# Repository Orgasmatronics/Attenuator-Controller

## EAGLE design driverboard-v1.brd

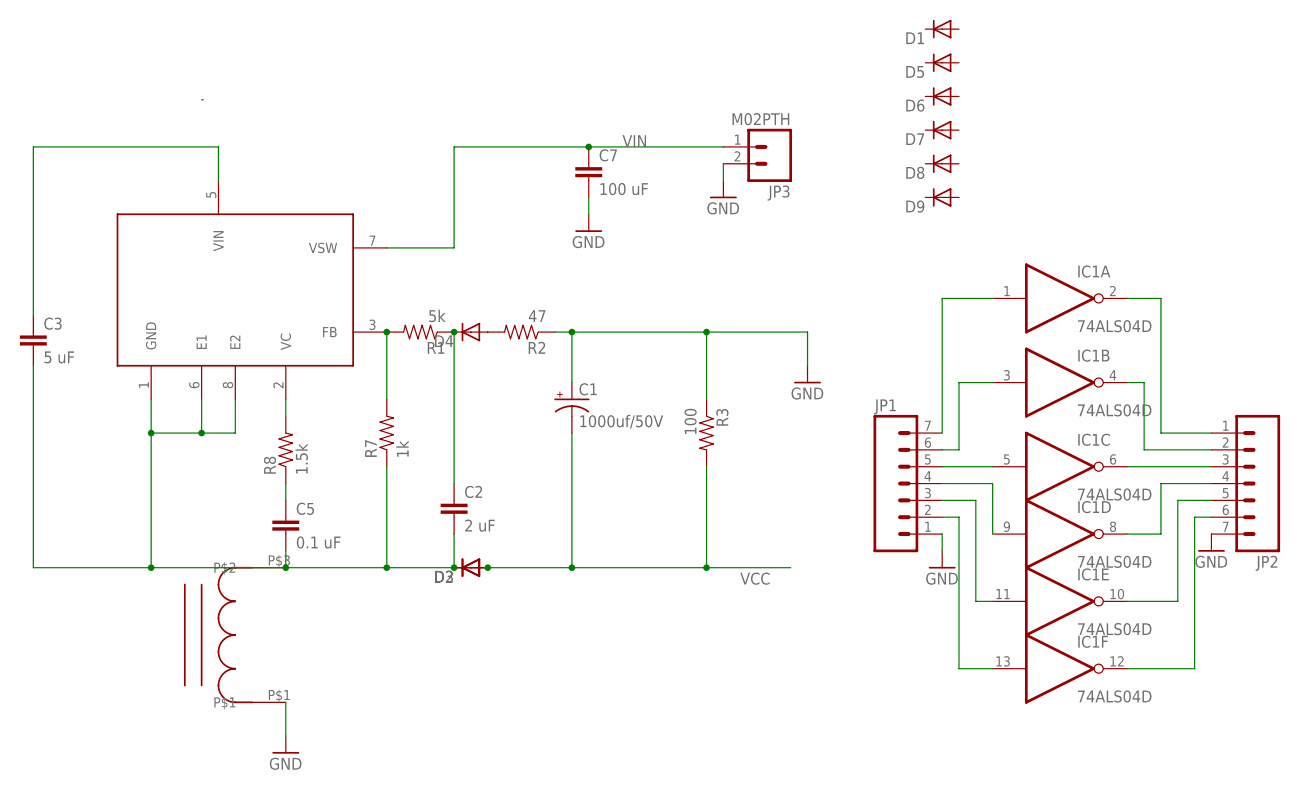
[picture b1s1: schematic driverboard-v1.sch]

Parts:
C1: 1000uf/50V; CPOL-RADIAL-1000UF-25V-KIT
C2: 2 uF; 0805
C3: 5 uF; 0805
C5: 0.1 uF; 0805
C7: 100 uF; 1206
D1, D2, D3, D4, D5, D6, D7, D8, D9: DIODE-DO-214AC; DO-214AC
IC1: 74ALS04D; SO14
JP1, JP2: M07; 1X07
JP3: M02PTH; 1X02
L2: 52626-L
R1: 5k; 0603-RES
R2: 47; 0603-RES
R3: 100; 0603-RES
R7: 1k; 0603-RES
R8: 1.5k; 0603-RES
U3: 1072-BOOST

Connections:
GND: C1.+, C7.2, IC1.7 (GND), JP1.1, JP2.7, JP3.2, L2.P$1, R2.1, R3.1
unnamed: IC1.1 (I), JP1.7
unnamed: R1.2, R7.2, U3.3 (FB)
unnamed: C2.1, D4.C, R1.1
unnamed: C3.1, U3.5 (VIN)
unnamed: C5.1, R8.1
unnamed: D4.A, R2.2
unnamed: C2.2, C3.2, C5.2, D2.C, D3.C, L2.P$3, R7.1, U3.1 (GND), U3.6 (E1), U3.8 (E2)
unnamed: IC1.3 (I), JP1.6
unnamed: IC1.5 (I), JP1.5
unnamed: IC1.9 (I), JP1.4
unnamed: IC1.11 (I), JP1.3
unnamed: IC1.13 (I), JP1.2
unnamed: IC1.12 (O), JP2.6
unnamed: IC1.10 (O), JP2.5
unnamed: IC1.8 (O), JP2.4
unnamed: IC1.6 (O), JP2.3
unnamed: IC1.4 (O), JP2.2
unnamed: IC1.2 (O), JP2.1
unnamed: R8.2, U3.2 (VC)
VCC: C1.-, D2.A, D3.A, IC1.14 (VCC), R3.2
VIN: C7.1, JP3.1, U3.7 (VSW)

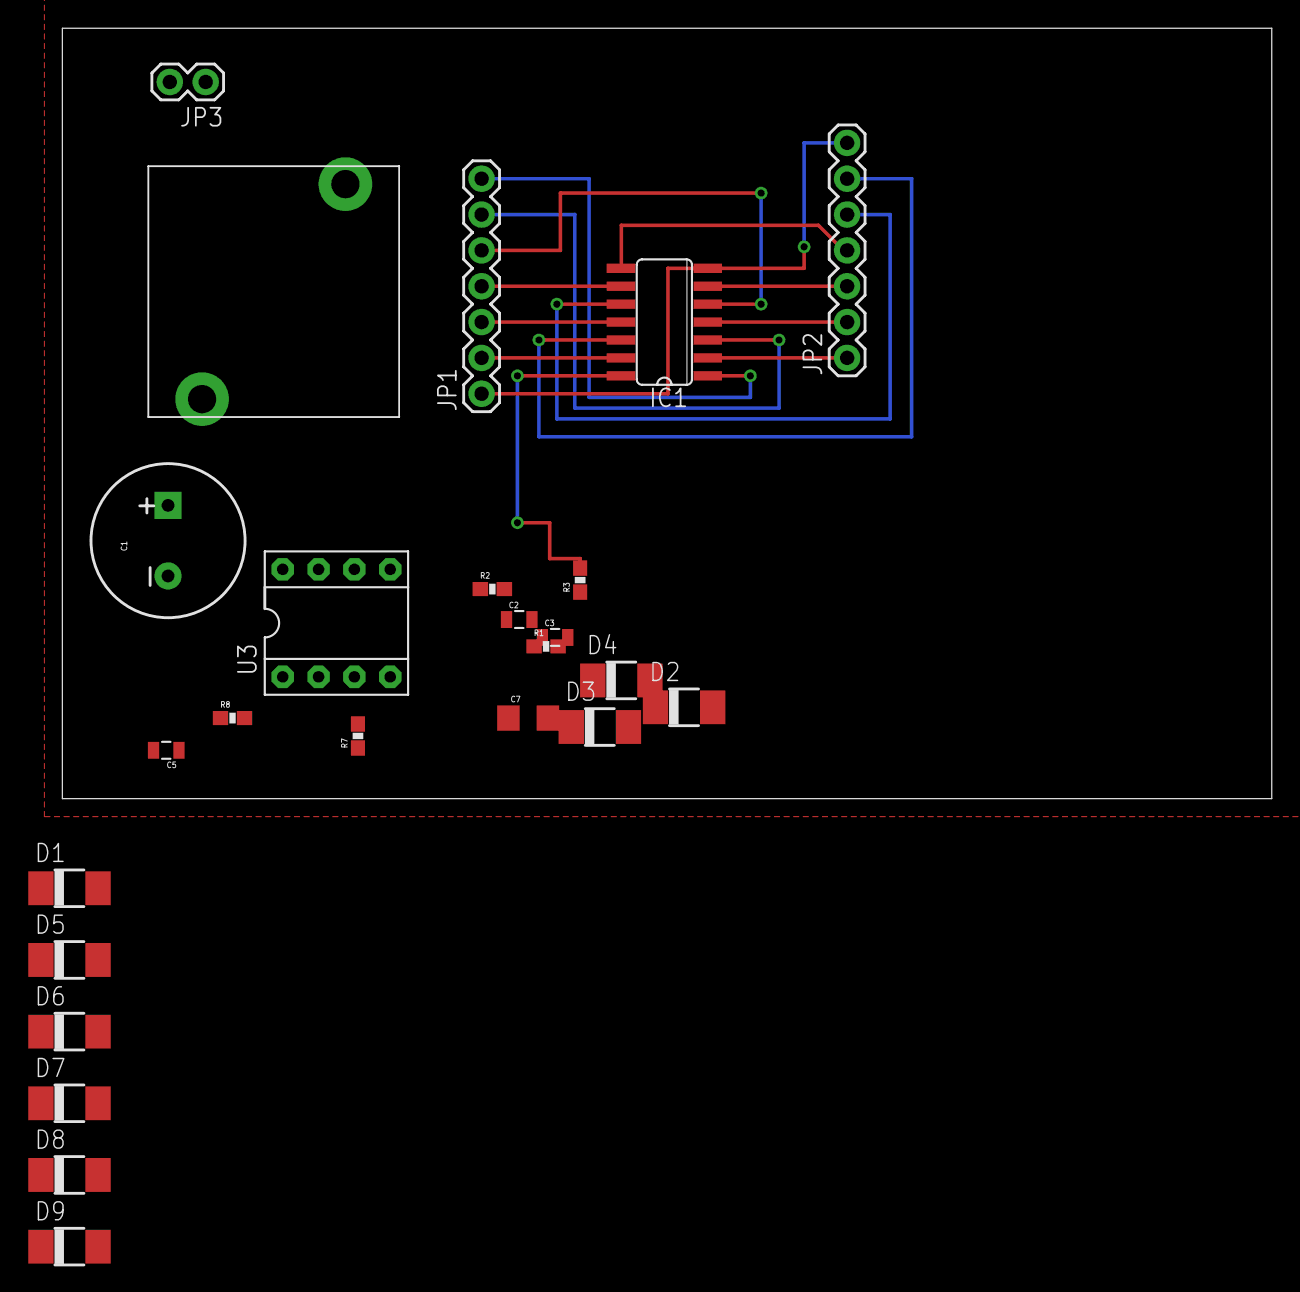
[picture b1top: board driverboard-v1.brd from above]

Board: 2 copper layers, 85.7 x 54.6 mm, 25 parts (0 on the bottom side), 22 nets.

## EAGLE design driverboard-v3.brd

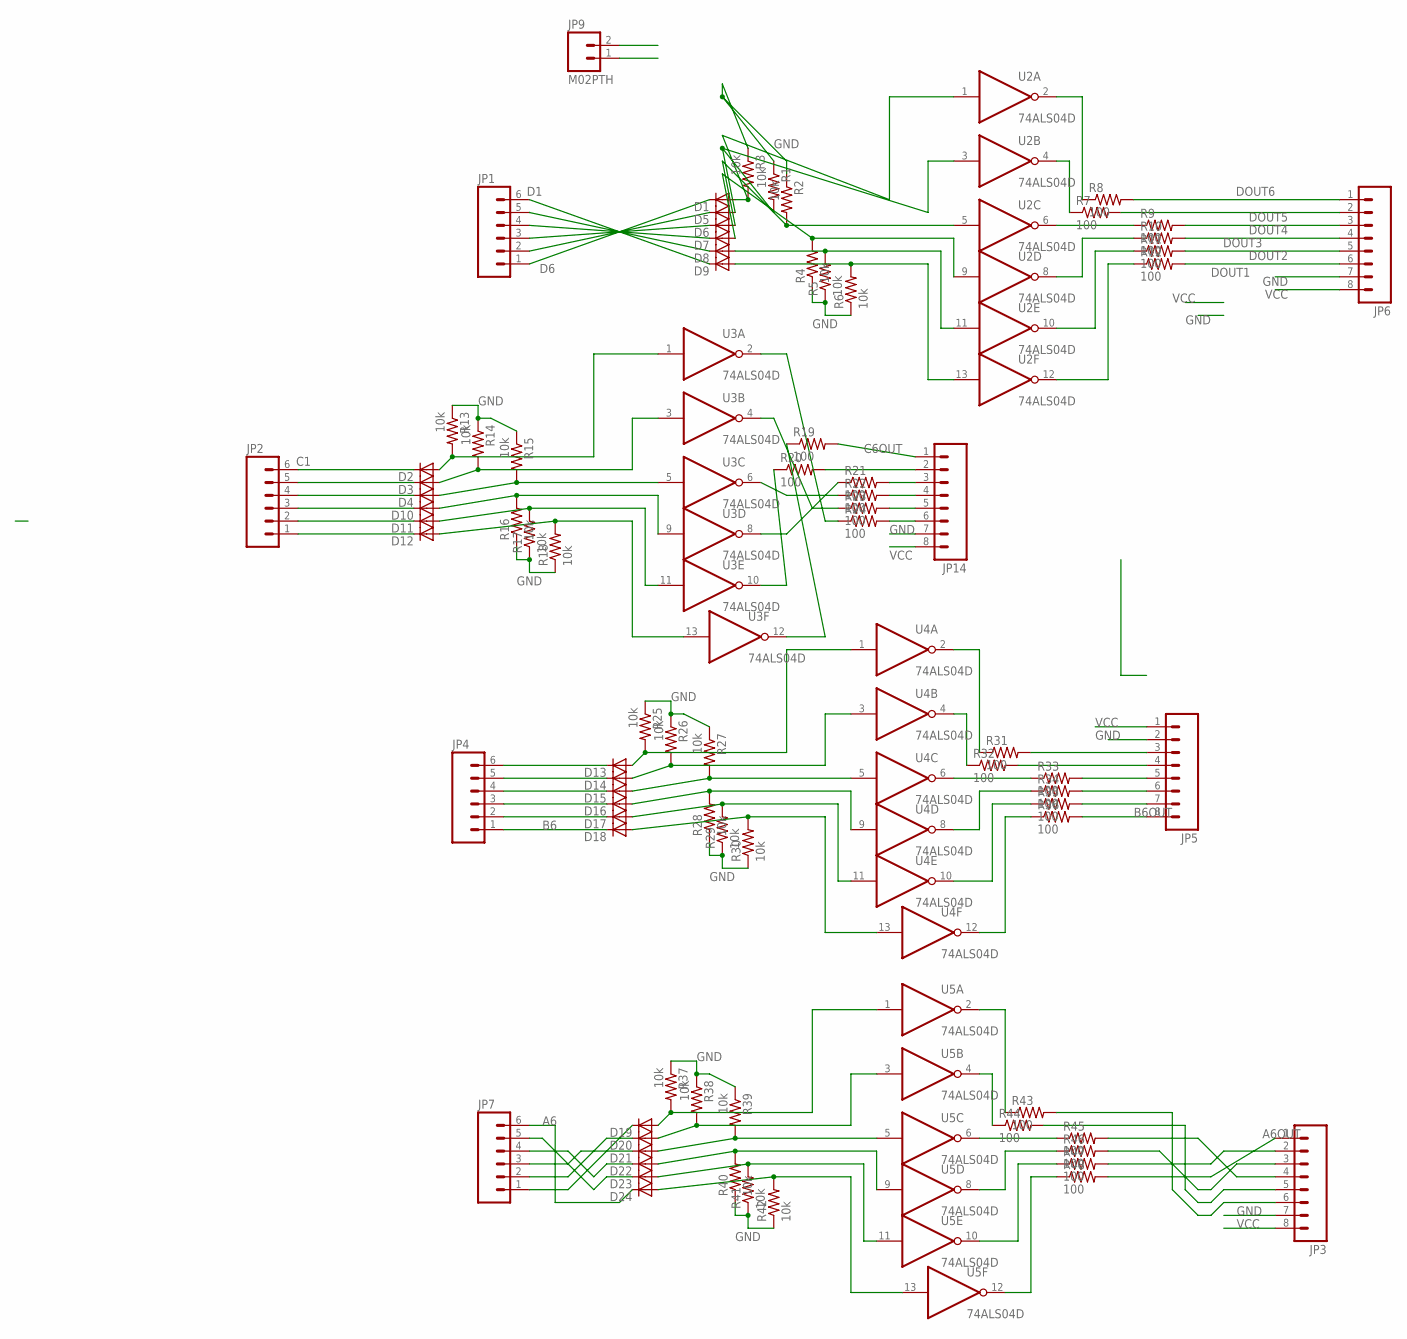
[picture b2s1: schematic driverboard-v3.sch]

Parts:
D1, D2, D3, D4, D5, D6, D7, D8, D9, D10, D11, D12, D13, D14, D15, D16, D17, D18, D19, D20, D21, D22, D23, D24: DIODE-DO-214AC; DO-214AC
JP1, JP2, JP4, JP7: M06NO_SILK; 1X06_NO_SILK
JP3, JP5, JP6, JP14: M08NO_SILK; 1X08_NO_SILK
JP9: M02PTH; 1X02
R1, R2, R3, R4, R5, R6, R13, R14, R15, R16, R17, R18, R25, R26, R27, R28, R29, R30, R37, R38, R39, R40, R41, R42: 10k; 0603-RES
R7, R8, R9, R10, R11, R12, R19, R20, R21, R22, R23, R24, R31, R32, R33, R34, R35, R36, R43, R44, R45, R46, R47, R48: 100; 0603-RES
U2, U3, U4, U5: 74ALS04D; SO14

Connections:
A1: D19.C, JP7.1
A1OUT: JP3.6, R43.2
A2: D20.C, JP7.2
A2OUT: JP3.5, R44.2
A3: D21.C, JP7.3
A3OUT: JP3.4, R45.2
A4: D22.C, JP7.4
A4OUT: JP3.3, R46.2
A5: D23.C, JP7.5
A5OUT: JP3.2, R47.2
A6: D24.C, JP7.6
A6OUT: JP3.1, R48.2
B1: D13.C, JP4.6
B1OUT: JP5.3, R31.2
B2: D14.C, JP4.5
B2OUT: JP5.4, R32.2
B3: D15.C, JP4.4
B3OUT: JP5.5, R33.2
B4: D16.C, JP4.3
B4OUT: JP5.6, R34.2
B5: D17.C, JP4.2
B5OUT: JP5.7, R35.2
B6: D18.C, JP4.1
B6OUT: JP5.8, R36.2
C1: D2.C, JP2.6
C1OUT: JP14.6, R24.2
C2: D3.C, JP2.5
C2OUT: JP14.5, R23.2
C3: D4.C, JP2.4
C3OUT: JP14.4, R22.2
C4: D10.C, JP2.3
C4OUT: JP14.3, R21.2
C5: D11.C, JP2.2
C5OUT: JP14.2, R20.2
C6: D12.C, JP2.1
C6OUT: JP14.1, R19.2
D1: D9.C, JP1.6
D2: D8.C, JP1.5
D3: D7.C, JP1.4
D4: D6.C, JP1.3
D5: D5.C, JP1.2
D6: D1.C, JP1.1
DOUT1: JP6.6, R12.2
DOUT2: JP6.5, R11.2
DOUT3: JP6.4, R10.2
DOUT4: JP6.3, R9.2
DOUT5: JP6.2, R7.2
DOUT6: JP6.1, R8.2
GND: JP3.7, JP5.2, JP6.7, JP9.1, JP14.7, R1.1, R2.1, R3.1, R4.1, R5.1, R6.1, R13.1, R14.1, R15.1, R16.1, R17.1, R18.1, R25.1, R26.1, R27.1, R28.1, R29.1, R30.1, R37.1, R38.1, R39.1, R40.1, R41.1, R42.1, U2.7 (GND), U3.7 (GND), U4.7 (GND), U5.7 (GND)
unnamed: R19.1, U3.12 (O)
unnamed: R20.1, U3.10 (O)
unnamed: R21.1, U3.8 (O)
unnamed: D1.A, R3.2, U2.1 (I)
unnamed: D5.A, R1.2, U2.3 (I)
unnamed: D7.A, R4.2, U2.9 (I)
unnamed: R12.1, U2.12 (O)
unnamed: R11.1, U2.10 (O)
unnamed: R10.1, U2.8 (O)
unnamed: R9.1, U2.6 (O)
unnamed: R7.1, U2.4 (O)
unnamed: R8.1, U2.2 (O)
unnamed: D6.A, R2.2, U2.5 (I)
unnamed: D8.A, R5.2, U2.11 (I)
unnamed: D9.A, R6.2, U2.13 (I)
unnamed: D3.A, R14.2, U3.3 (I)
unnamed: D10.A, R16.2, U3.9 (I)
unnamed: R22.1, U3.6 (O)
unnamed: R23.1, U3.4 (O)
unnamed: R24.1, U3.2 (O)
unnamed: D2.A, R13.2, U3.1 (I)
unnamed: D4.A, R15.2, U3.5 (I)
unnamed: D11.A, R17.2, U3.11 (I)
unnamed: D12.A, R18.2, U3.13 (I)
unnamed: D14.A, R26.2, U4.3 (I)
unnamed: D16.A, R28.2, U4.9 (I)
unnamed: R36.1, U4.12 (O)
unnamed: R35.1, U4.10 (O)
unnamed: R34.1, U4.8 (O)
unnamed: R33.1, U4.6 (O)
unnamed: R32.1, U4.4 (O)
unnamed: R31.1, U4.2 (O)
unnamed: D13.A, R25.2, U4.1 (I)
unnamed: D15.A, R27.2, U4.5 (I)
unnamed: D17.A, R29.2, U4.11 (I)
unnamed: D18.A, R30.2, U4.13 (I)
unnamed: D20.A, R38.2, U5.3 (I)
unnamed: D22.A, R40.2, U5.9 (I)
unnamed: R48.1, U5.12 (O)
unnamed: R47.1, U5.10 (O)
unnamed: R46.1, U5.8 (O)
unnamed: R45.1, U5.6 (O)
unnamed: R44.1, U5.4 (O)
unnamed: R43.1, U5.2 (O)
unnamed: D19.A, R37.2, U5.1 (I)
unnamed: D21.A, R39.2, U5.5 (I)
unnamed: D23.A, R41.2, U5.11 (I)
unnamed: D24.A, R42.2, U5.13 (I)
VCC: JP3.8, JP5.1, JP6.8, JP9.2, JP14.8, U2.14 (VCC), U3.14 (VCC), U4.14 (VCC), U5.14 (VCC)

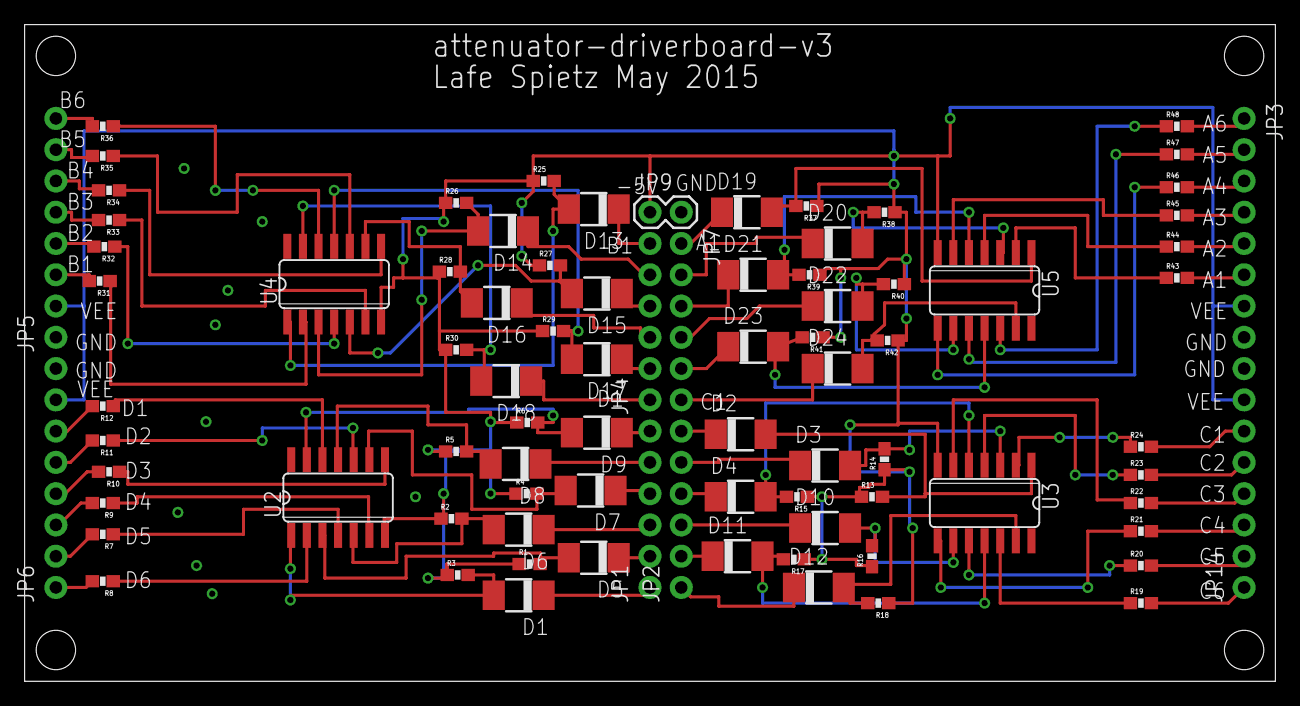
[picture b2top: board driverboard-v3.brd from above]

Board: 2 copper layers, 101.6 x 53.3 mm, 85 parts (0 on the bottom side), 98 nets.

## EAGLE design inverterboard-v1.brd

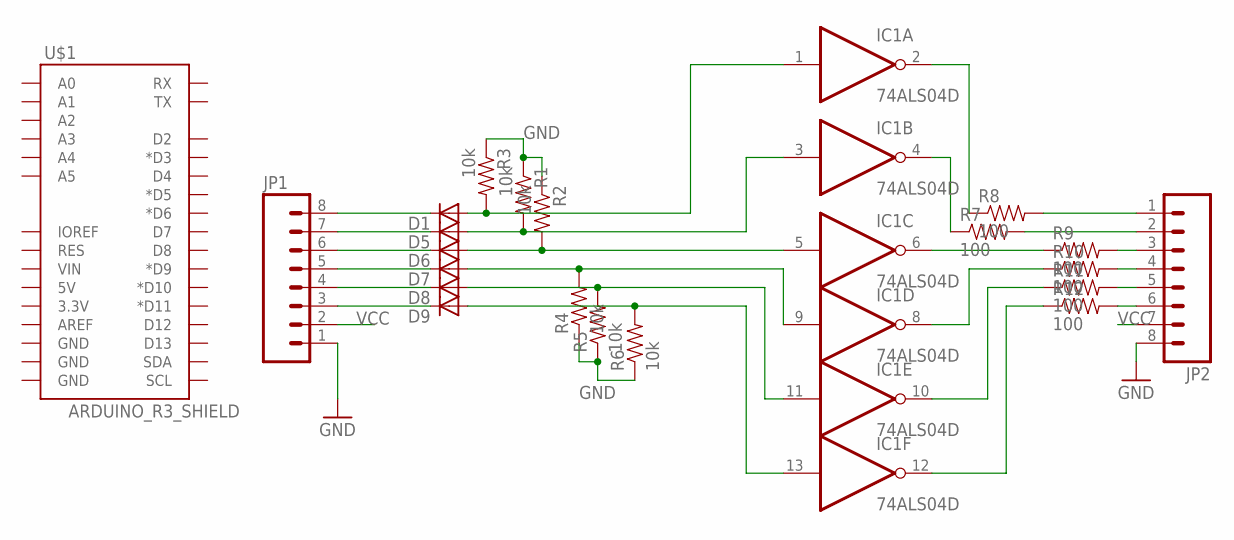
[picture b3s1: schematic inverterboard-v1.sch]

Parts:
D1, D5, D6, D7, D8, D9: DIODE-DO-214AC; DO-214AC
IC1: 74ALS04D; SO14
JP1, JP2: M081X08; 1X08
R1, R2, R3, R4, R5, R6: 10k; 0603-RES
R7, R8, R9, R10, R11, R12: 100; 0603-RES
U$1: ARDUINO_R3_SHIELD; UNO_R3_SHIELD

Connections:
GND: IC1.7 (GND), JP1.1, JP2.8, R1.1, R2.1, R3.1, R4.1, R5.1, R6.1
unnamed: D5.C, JP1.7
unnamed: JP2.1, R8.2
unnamed: D1.C, JP1.8
unnamed: D6.C, JP1.6
unnamed: D7.C, JP1.5
unnamed: D8.C, JP1.4
unnamed: D9.C, JP1.3
unnamed: D1.A, IC1.1 (I), R3.2
unnamed: D5.A, IC1.3 (I), R1.2
unnamed: JP2.2, R7.2
unnamed: D7.A, IC1.9 (I), R4.2
unnamed: JP2.3, R9.2
unnamed: JP2.4, R10.2
unnamed: IC1.12 (O), R12.1
unnamed: IC1.10 (O), R11.1
unnamed: IC1.8 (O), R10.1
unnamed: IC1.6 (O), R9.1
unnamed: IC1.4 (O), R7.1
unnamed: IC1.2 (O), R8.1
unnamed: D6.A, IC1.5 (I), R2.2
unnamed: JP2.5, R11.2
unnamed: D8.A, IC1.11 (I), R5.2
unnamed: D9.A, IC1.13 (I), R6.2
unnamed: JP2.6, R12.2
VCC: IC1.14 (VCC), JP1.2, JP2.7

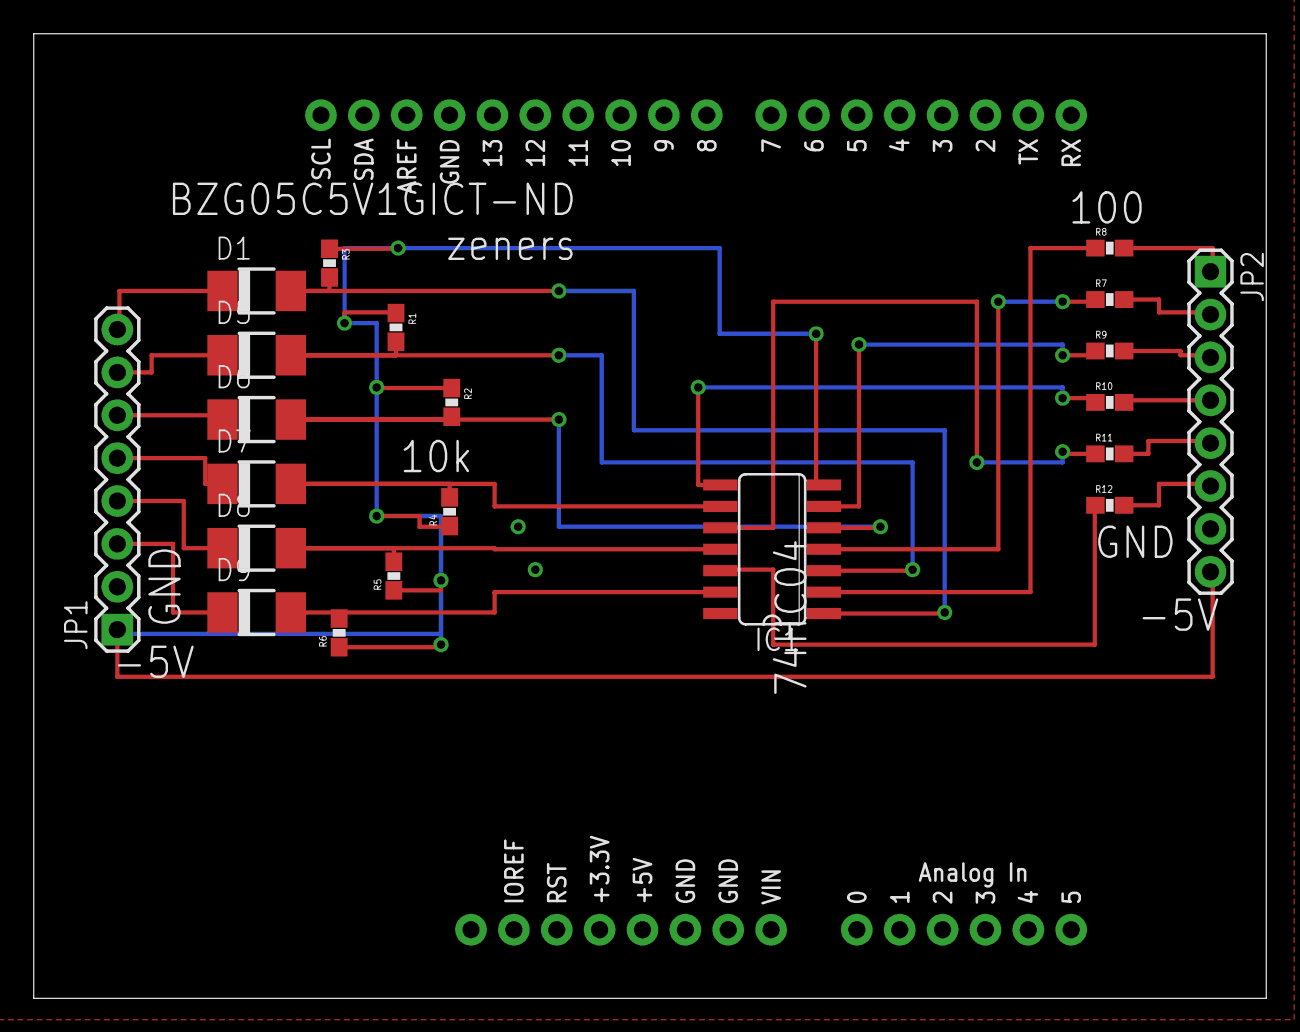
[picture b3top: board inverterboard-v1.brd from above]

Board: 2 copper layers, 73.0 x 57.1 mm, 22 parts (0 on the bottom side), 26 nets.

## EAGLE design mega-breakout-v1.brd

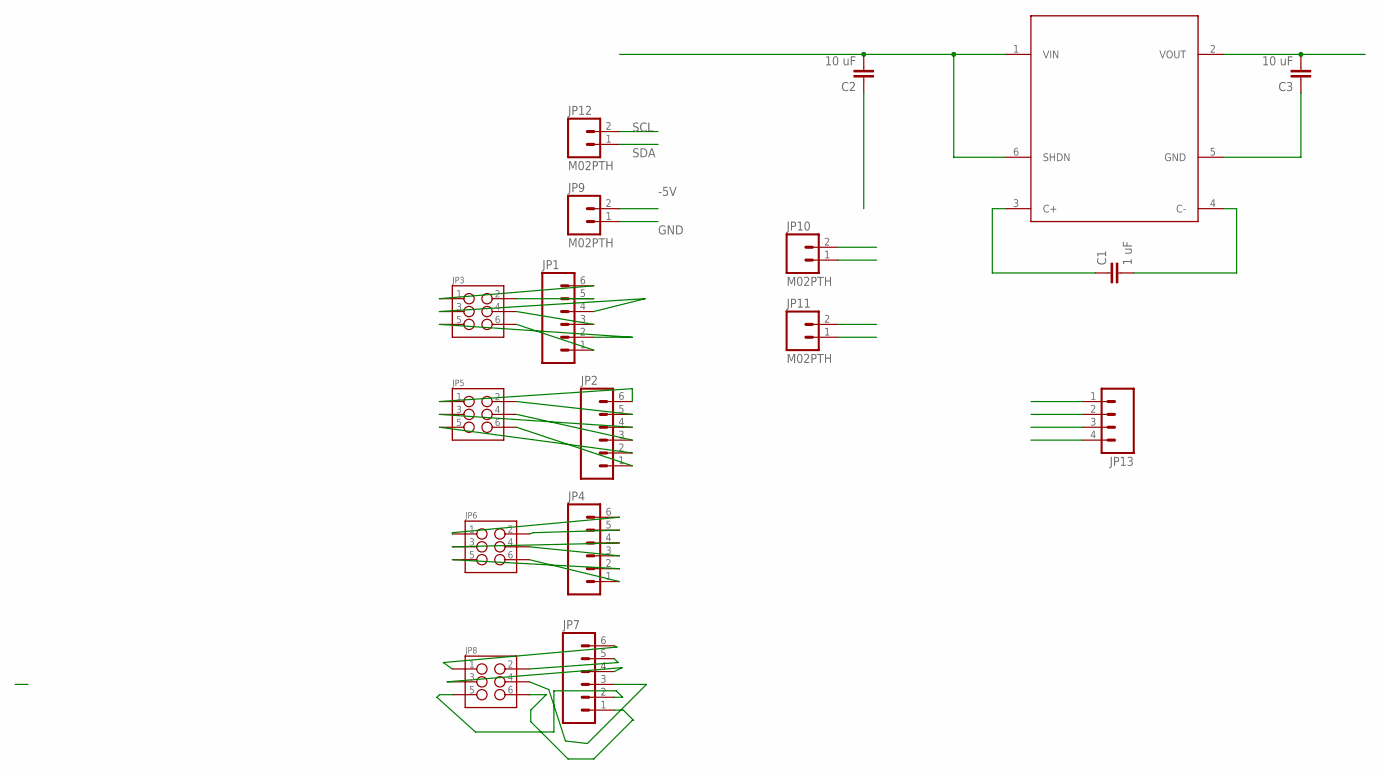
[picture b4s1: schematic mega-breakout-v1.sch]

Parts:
C1: 1 uF; 0805
C2, C3: 10 uF; 0805
JP1, JP2, JP4, JP7: M06NO_SILK; 1X06_NO_SILK
JP3, JP5, JP6, JP8: M03X22X3_SILK_SM; 2X3
JP9, JP10, JP11, JP12: M02PTH; 1X02
JP13: M04PTH; 1X04
U1: LTC1983; SSOT23-6

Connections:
-5V: C3.2, JP9.2, U1.2 (VOUT)
A1: JP7.6, JP8.1
A2: JP7.5, JP8.2
A3: JP7.4, JP8.3
A4: JP7.3, JP8.4
A5: JP7.2, JP8.5
A6: JP7.1, JP8.6
B1: JP4.6, JP6.1
B2: JP4.5, JP6.2
B3: JP4.4, JP6.3
B4: JP4.3, JP6.4
B5: JP4.2, JP6.5
B6: JP4.1, JP6.6
C1: JP2.6, JP5.1
C2: JP2.5, JP5.2
C3: JP2.4, JP5.3
C4: JP2.3, JP5.4
C5: JP2.2, JP5.5
C6: JP2.1, JP5.6
D1: JP1.6, JP3.1
D2: JP1.5, JP3.2
D3: JP1.4, JP3.3
D4: JP1.3, JP3.4
D5: JP1.2, JP3.5
D6: JP1.1, JP3.6
GND: JP9.1, JP13.3
unnamed: C1.2, U1.4 (C-)
unnamed: C1.1, U1.3 (C+)
SCL: JP12.2, JP13.2
SDA: JP12.1, JP13.1
VCC: C2.2, JP11.1, JP11.2, JP13.4, U1.1 (VIN), U1.6 (SHDN)
VCC1: C2.1, C3.1, U1.5 (GND)

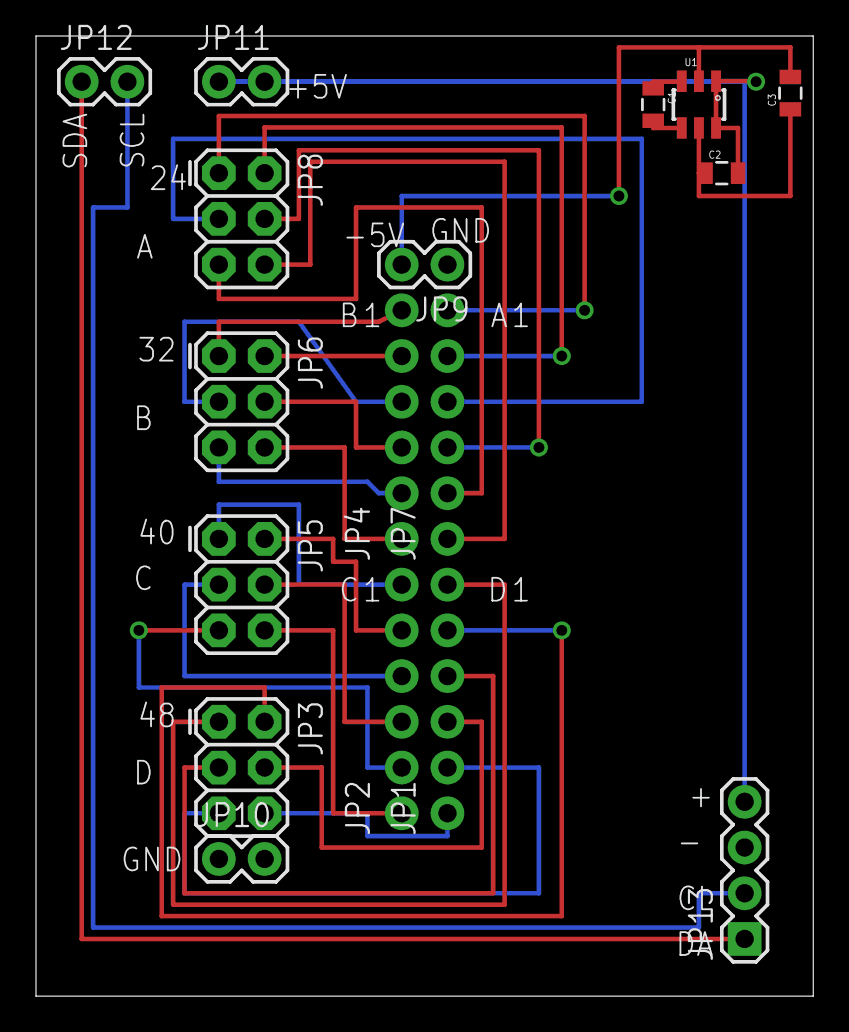
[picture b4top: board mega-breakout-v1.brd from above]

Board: 2 copper layers, 43.2 x 53.3 mm, 17 parts (0 on the bottom side), 32 nets.

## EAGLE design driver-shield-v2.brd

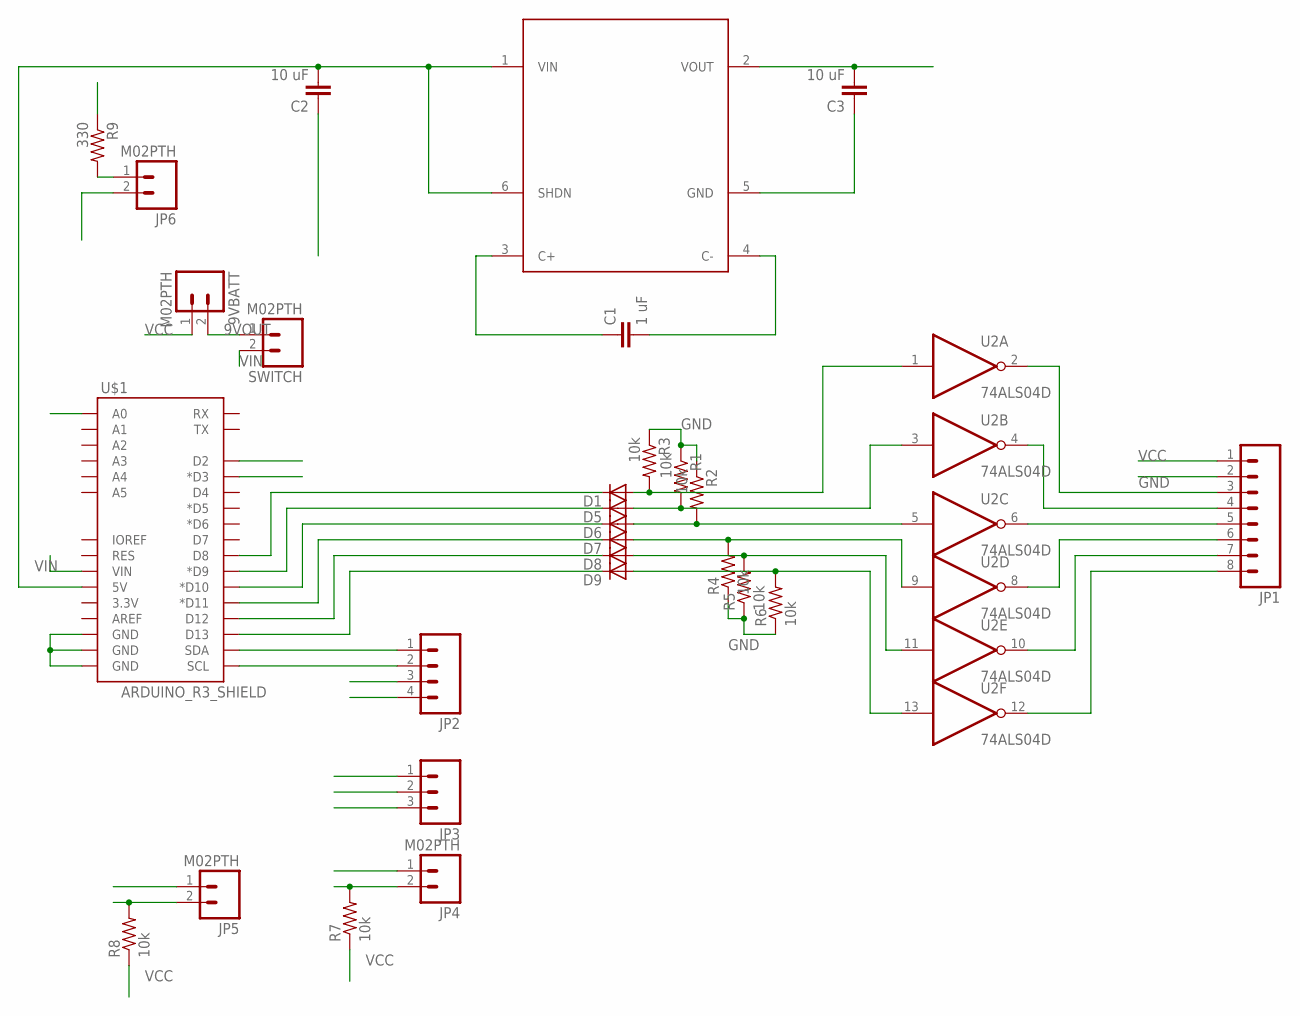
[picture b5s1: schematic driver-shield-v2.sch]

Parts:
9VBATT: M02PTH; 1X02
C1: 1 uF; 0805
C2, C3: 10 uF; 0805
D1, D5, D6, D7, D8, D9: DIODE-DO-214AC; DO-214AC
JP1: M081X08; 1X08
JP2: M04PTH; 1X04
JP3: M03PTH; 1X03
JP4, JP5, JP6: M02PTH; 1X02
R1, R2, R3, R4, R5, R6, R7, R8: 10k; 0603-RES
R9: 330; 0603-RES
SWITCH: M02PTH; 1X02
U1: LTC1983; SSOT23-6
U2: 74ALS04D; SO14
U$1: ARDUINO_R3_SHIELD; UNO_R3_SHIELD

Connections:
9VOUT: 9VBATT.2, SWITCH.1
+5V: C2.2, JP2.4, JP3.1, JP4.1, R9.1, U1.1 (VIN), U1.6 (SHDN), U$1.5V
+5V1: JP5.1
A0: JP3.2, U$1.A0
D2: JP4.2, R7.2, U$1.D2
D3: JP5.2, R8.2, U$1.D3 (*D3)
GND: C3.2, JP1.2, R1.1, R2.1, R3.1, R4.1, R5.1, R6.1, U1.2 (VOUT), U2.7 (GND)
unnamed: D5.C, U$1.D9 (*D9)
unnamed: JP2.1, U$1.SDA
unnamed: D1.C, U$1.D8
unnamed: D6.C, U$1.D10 (*D10)
unnamed: D7.C, U$1.D11 (*D11)
unnamed: D8.C, U$1.D12
unnamed: D9.C, U$1.D13
unnamed: D1.A, R3.2, U2.1 (I)
unnamed: D5.A, R1.2, U2.3 (I)
unnamed: JP2.2, U$1.SCL
unnamed: D7.A, R4.2, U2.9 (I)
unnamed: JP6.1, R9.2
unnamed: JP1.6, U2.8 (O)
unnamed: JP1.8, U2.12 (O)
unnamed: JP1.7, U2.10 (O)
unnamed: JP1.5, U2.6 (O)
unnamed: JP1.4, U2.4 (O)
unnamed: JP1.3, U2.2 (O)
unnamed: D6.A, R2.2, U2.5 (I)
unnamed: D8.A, R5.2, U2.11 (I)
unnamed: D9.A, R6.2, U2.13 (I)
unnamed: C1.2, U1.4 (C-)
unnamed: C1.1, U1.3 (C+)
VCC: 9VBATT.1, C2.1, C3.1, JP1.1, JP2.3, JP3.3, JP6.2, R7.1, R8.1, U1.5 (GND), U2.14 (VCC), U$1.GND@0 (GND), U$1.GND@1 (GND), U$1.GND@2 (GND)
VIN: SWITCH.2, U$1.VIN

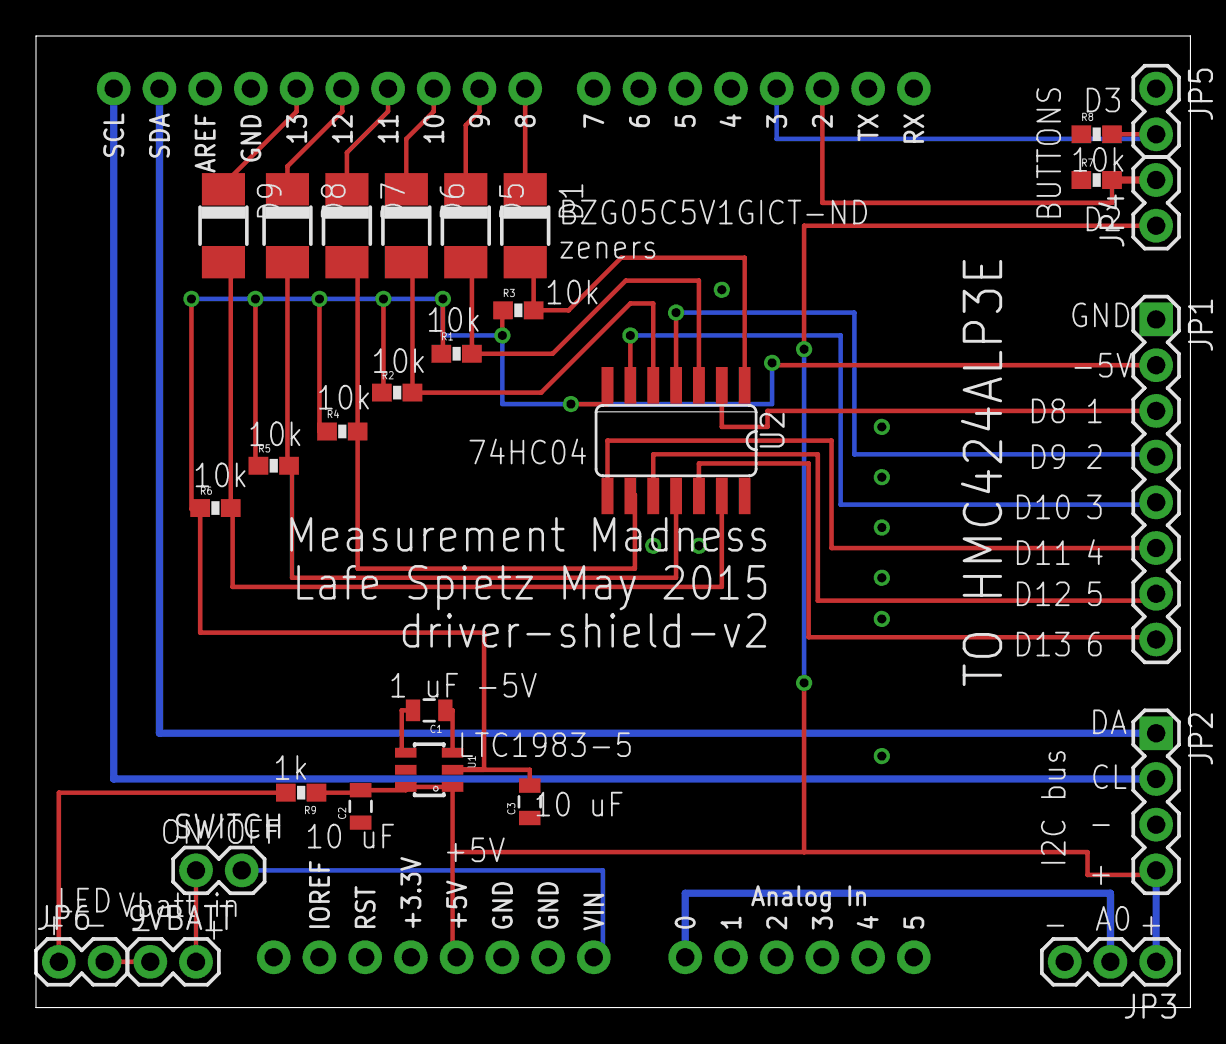
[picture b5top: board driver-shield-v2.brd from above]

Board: 2 copper layers, 64.1 x 54.0 mm, 29 parts (0 on the bottom side), 31 nets.

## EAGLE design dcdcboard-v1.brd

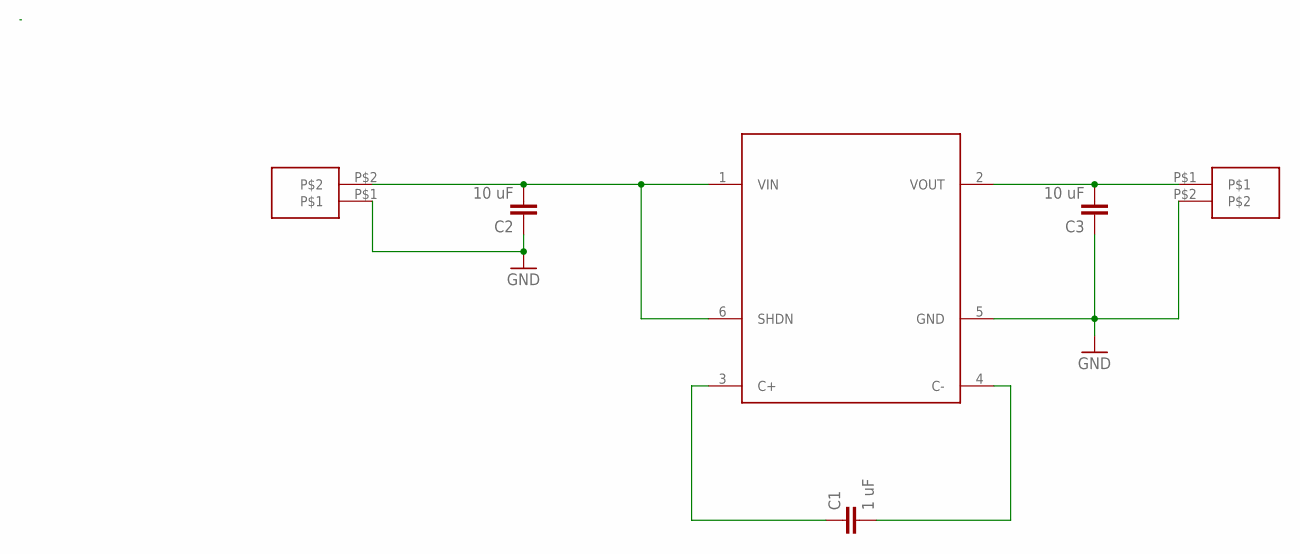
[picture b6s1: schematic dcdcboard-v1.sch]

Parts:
C1: 1 uF; 0805
C2, C3: 10 uF; 0805
U$1: LTC1983; SSOT23-6
U$2, U$3: SPRING-TERMINAL

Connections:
GND: C2.1, C3.1, U$1.5 (GND), U$2.P$1, U$3.P$2
unnamed: C1.2, U$1.4 (C-)
unnamed: C1.1, U$1.3 (C+)
VIN: C2.2, U$1.1 (VIN), U$1.6 (SHDN), U$2.P$2
VOUT: C3.2, U$1.2 (VOUT), U$3.P$1

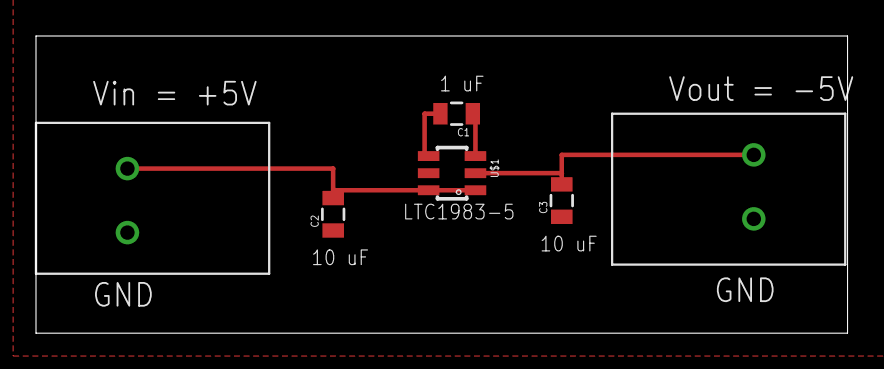
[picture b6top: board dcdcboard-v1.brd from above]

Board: 2 copper layers, 45.1 x 16.5 mm, 6 parts (0 on the bottom side), 5 nets.

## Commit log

2015-12-02 :circus_tent: Added .gitattributes & .gitignore files
2015-12-02 added entire folder from the project
    organization is poor, sorry, but it's all here, will try to add
    documentation eventually

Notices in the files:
parts and their libraries:
SparkFun-Capacitors: Licensing: CC v3.0 Share-Alike You are welcome to use this library for commercial purposes.
SparkFun-Aesthetics: Licensing: Creative Commons ShareAlike 4.0 International - https://creativecommons.org/licenses/by-sa/4.0
